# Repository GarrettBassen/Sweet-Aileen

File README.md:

# Sweet-Aileen
Guitar Pedal for Electronics 2 Final Project

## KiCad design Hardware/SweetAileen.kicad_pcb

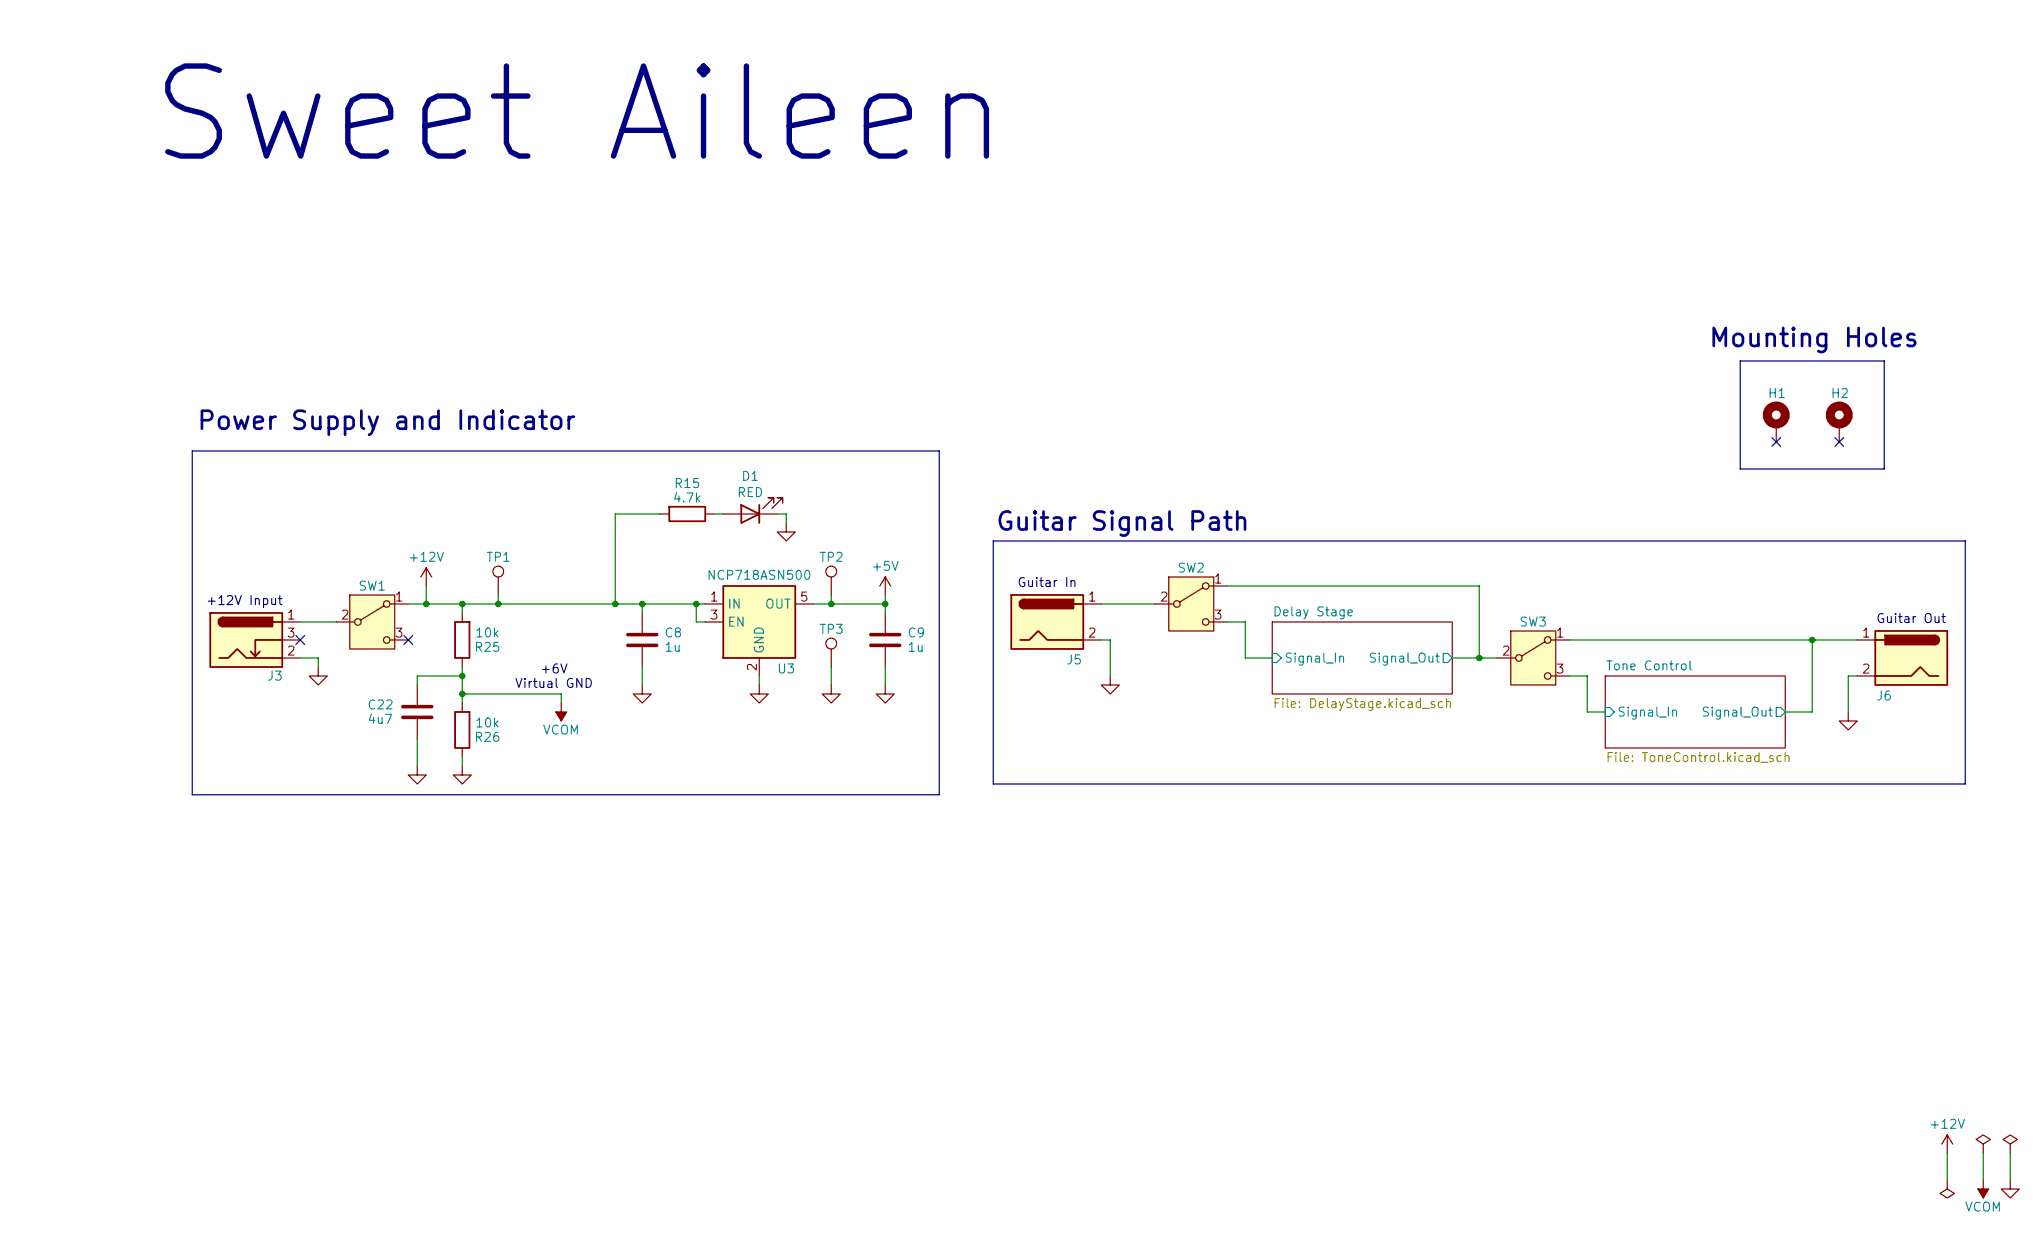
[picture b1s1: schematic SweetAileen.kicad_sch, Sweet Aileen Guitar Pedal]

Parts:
C8, C9: 1u; C_0402_1005Metric
C22: 4u7; C_0805_2012Metric
D1: RED; Connector-Generic-2
H1, H2: MountingHole_Pad; MountingHole_2.5mm_Pad_TopBottom
J3: Barrel_Jack_Switch; 54-00166
J5, J6: Jack-DC; Connector-Generic-2
R15: 4.7k; R_0402_1005Metric
R25, R26: 10k; R_0402_1005Metric
SW1, SW2, SW3: SW_SPDT; Connector-Generic-3
TP1, TP2, TP3: TestPoint; TestPoint_Pad_D1.5mm
U3: NCP718ASN500; SOT-23-5

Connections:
+5V: C9.2, TP2.1 (1_1), U3.5 (OUT); also elsewhere on the board
+12V: C8.2, R15.2, R25.2, SW1.1 (A), TP1.1 (1_1), U3.1 (IN), U3.3 (EN); also elsewhere on the board
/Delay Stage/Signal_In: SW2.3 (C); also elsewhere on the board
/Delay Stage/Signal_Out: SW2.1 (A), SW3.2 (B); also elsewhere on the board
/Tone Control/Signal_In: SW3.3 (C); also elsewhere on the board
/Tone Control/Signal_Out: J6.1, SW3.1 (A); also elsewhere on the board
GND: C8.1, C9.1, C22.1, D1.1 (K), J3.2, J5.2, J6.2, R26.1, TP3.1 (1_1), U3.2 (GND); also elsewhere on the board
unnamed: D1.2 (A), R15.1
unnamed: J3.1, SW1.2 (B)
unnamed: J5.1, SW2.2 (B)
VCOM: C22.2, R25.1, R26.2; also elsewhere on the board

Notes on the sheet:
+6V Virtual GND
Sweet Aileen
Guitar Signal Path
Mounting Holes
Power Supply and Indicator
Guitar In
Guitar Out
+12V Input

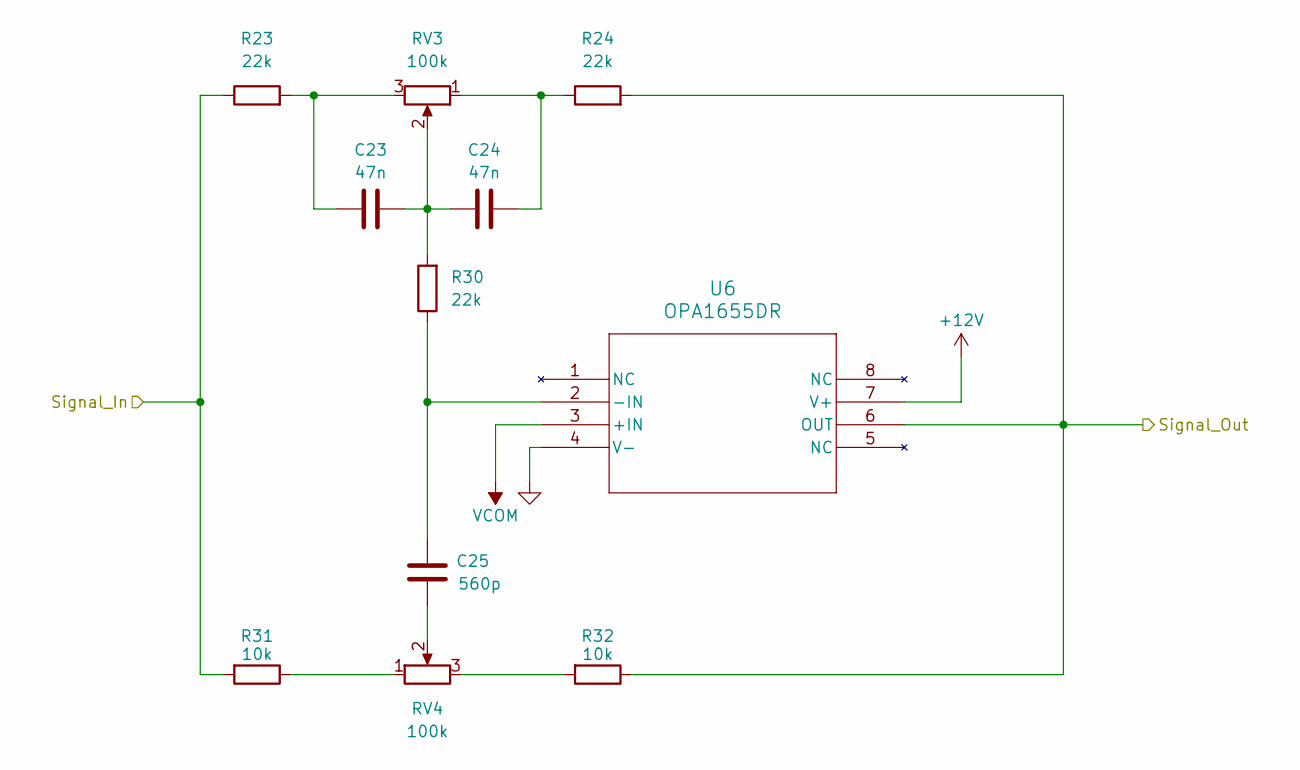
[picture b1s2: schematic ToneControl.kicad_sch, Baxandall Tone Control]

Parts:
C23, C24: 47n; C_0201_0603Metric
C25: 560p; C_0201_0603Metric
R23, R24, R30: 22k; R_0402_1005Metric
R31, R32: 10k; R_0402_1005Metric
RV3, RV4: 100k; Connector-Generic-3
U6: OPA1655DR

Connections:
+12V: U6.7 (V+); also elsewhere on the board
/Tone Control/Signal_In: R23.1, R31.2; also elsewhere on the board
/Tone Control/Signal_Out: R24.2, R32.1, U6.6 (OUT); also elsewhere on the board
GND: U6.4 (V-); also elsewhere on the board
unnamed: C23.1, R23.2, RV3.3
unnamed: C23.2, C24.1, R30.2, RV3.2
unnamed: C24.2, R24.1, RV3.1
unnamed: C25.2, RV4.2
unnamed: R31.1, RV4.1
unnamed: R32.2, RV4.3
unnamed: C25.1, R30.1, U6.2 (-IN)
VCOM: U6.3 (+IN); also elsewhere on the board

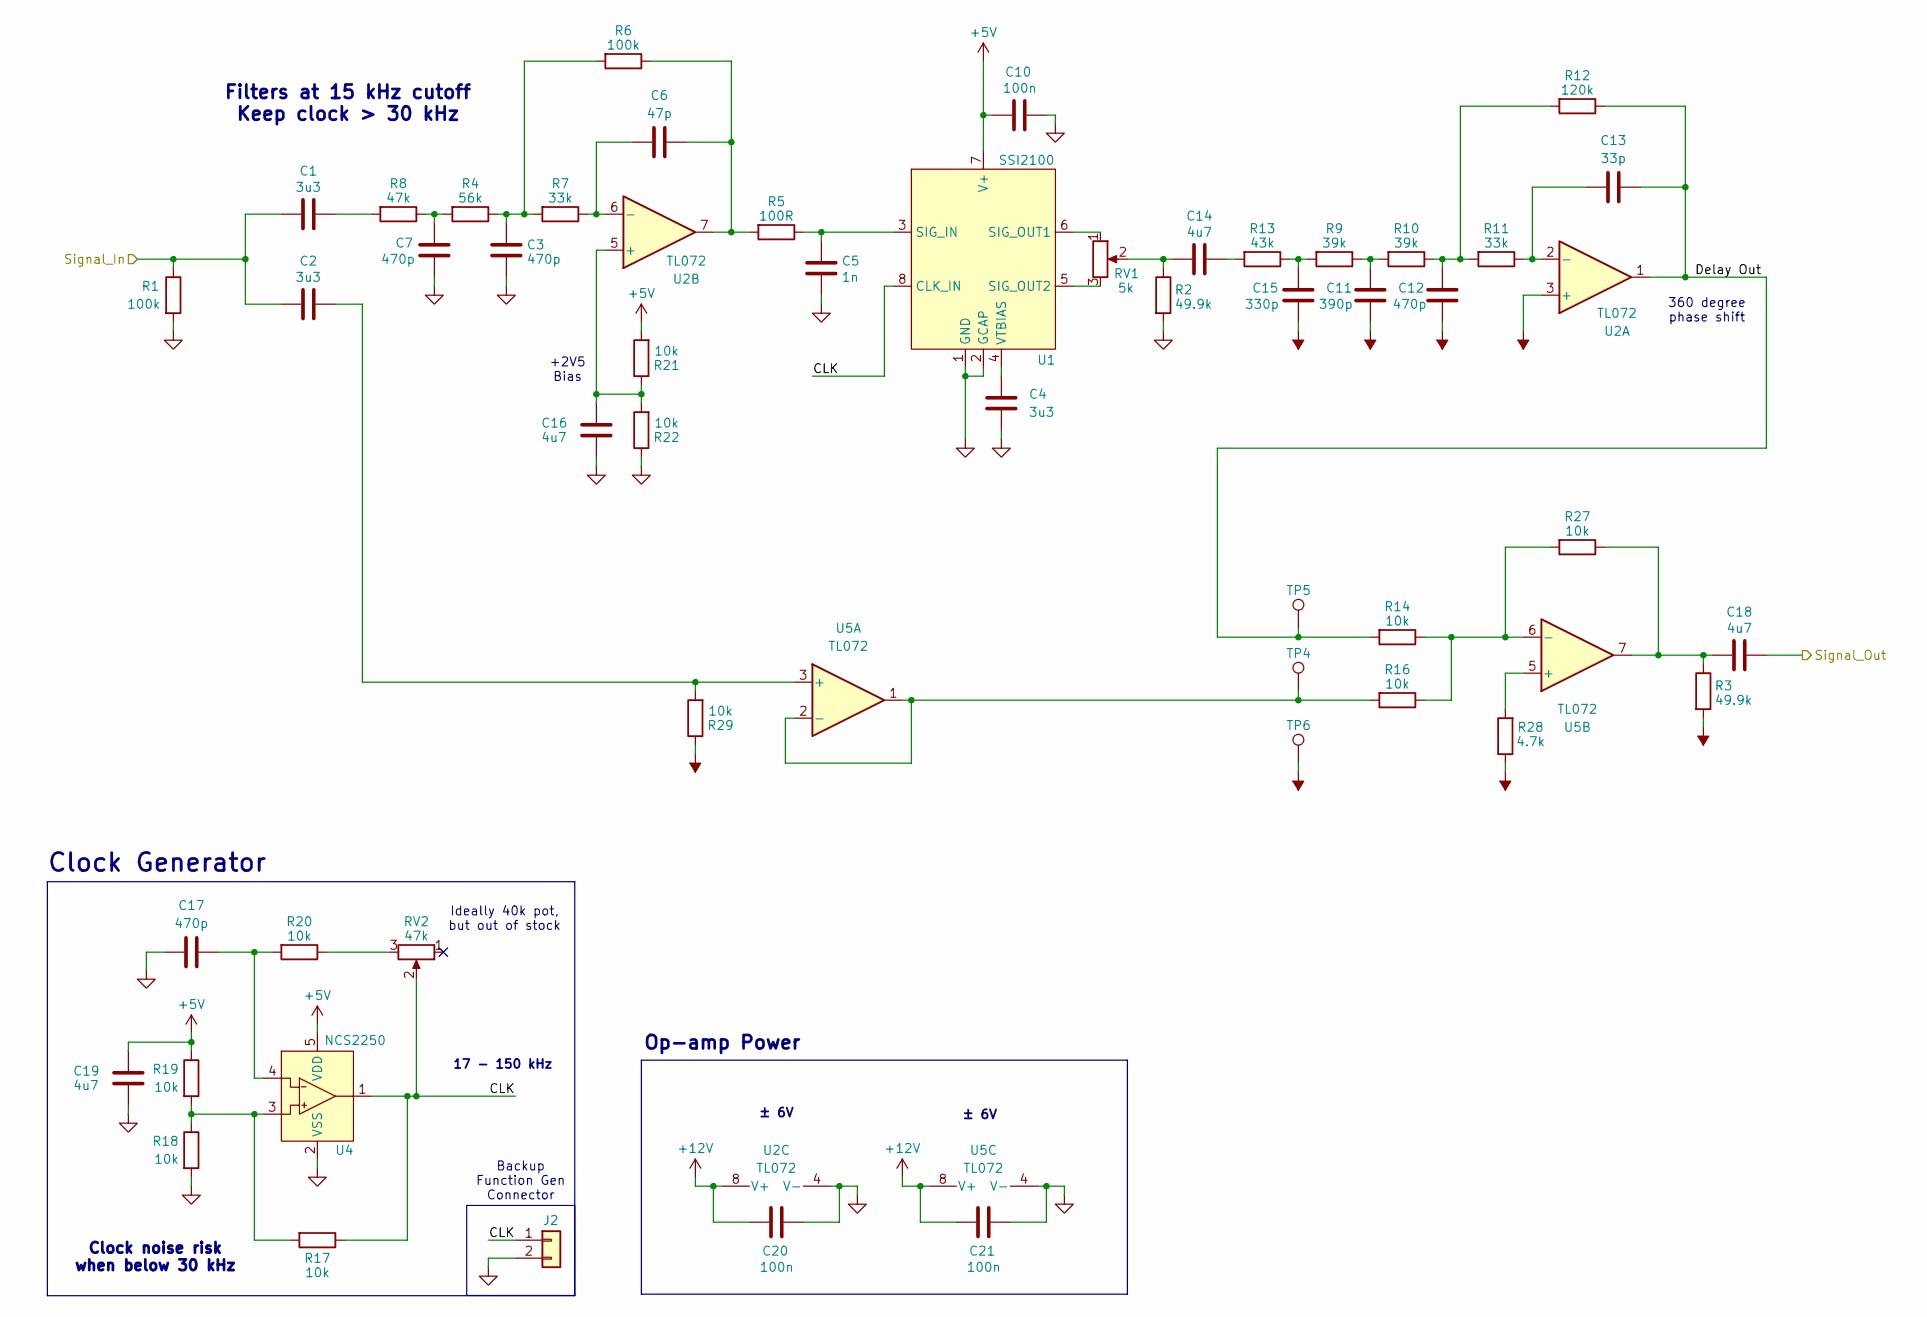
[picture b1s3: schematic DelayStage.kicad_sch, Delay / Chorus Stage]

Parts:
C1, C2, C4: 3u3; C_0805_2012Metric
C3, C7, C12, C17: 470p; C_0201_0603Metric
C5: 1n; C_0201_0603Metric
C6: 47p; C_0201_0603Metric
C10, C20, C21: 100n; C_0402_1005Metric
C11: 390p; C_0201_0603Metric
C13: 33p; C_0201_0603Metric
C14, C16, C18, C19: 4u7; C_0805_2012Metric
C15: 330p; C_0201_0603Metric
J2: Conn_01x02; Connector-Generic-2
R1, R6: 100k; R_0402_1005Metric
R2, R3: 49.9k; R_0402_1005Metric
R4: 56k; R_0402_1005Metric
R5: 100R; R_0402_1005Metric
R7, R11: 33k; R_0402_1005Metric
R8: 47k; R_0402_1005Metric
R9, R10: 39k; R_0402_1005Metric
R12: 120k; R_0402_1005Metric
R13: 43k; R_0402_1005Metric
R14, R16, R17, R18, R19, R20, R21, R22, R27, R29: 10k; R_0402_1005Metric
R28: 4.7k; R_0402_1005Metric
RV1: 5k; 3314G-1_BRN
RV2: 47k; Connector-Generic-3
TP4, TP5, TP6: TestPoint; TestPoint_Pad_D1.5mm
U1: SSI2100
U2, U5: TL072; SOIC-8_3.9x4.9mm_P1.27mm
U4: NCS2250; SOT-353_SC-70-5

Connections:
+5V: C10.2, C19.2, R19.1, R21.2, U1.7 (V+), U4.5 (VDD); also elsewhere on the board
+12V: C20.1, C21.1, U2.8 (V+), U5.8 (V+); also elsewhere on the board
/Delay Stage/CLK: J2.1, R17.1, RV2.2, U1.8 (CLK_IN), U4.1
/Delay Stage/Delay Out: C13.1, R12.1, R14.2, TP5.1 (1_1), U2.1
/Delay Stage/Signal_In: C1.1, C2.1, R1.1; also elsewhere on the board
/Delay Stage/Signal_Out: C18.2; also elsewhere on the board
GND: C3.1, C4.1, C5.1, C7.1, C10.1, C16.1, C17.2, C19.1, C20.2, C21.2, J2.2, R1.2, R2.2, R18.2, R22.1, U1.1 (GND), U1.2 (GCAP), U2.4 (V-), U4.2 (VSS), U5.4 (V-); also elsewhere on the board
unnamed: C1.2, R8.2
unnamed: C3.2, R4.1, R6.2, R7.2
unnamed: C6.1, R5.2, R6.1, U2.7
unnamed: C7.2, R4.2, R8.1
unnamed: C11.2, R9.1, R10.2
unnamed: C12.2, R10.1, R11.2, R12.2
unnamed: C14.1, R2.1, RV1.2
unnamed: C14.2, R13.2
unnamed: C15.2, R9.2, R13.1
unnamed: C17.1, R20.2, U4.4
unnamed: C18.1, R3.1, R27.1, U5.7
unnamed: R17.2, R18.1, R19.2, U4.3
unnamed: R20.1, RV2.3
unnamed: C5.2, R5.1, U1.3 (SIG_IN)
unnamed: RV1.1, U1.6 (SIG_OUT1)
unnamed: RV1.3, U1.5 (SIG_OUT2)
unnamed: C4.2, U1.4 (VTBIAS)
unnamed: C13.2, R11.1, U2.2 (-)
unnamed: C16.2, R21.1, R22.2, U2.5 (+)
unnamed: C6.2, R7.1, U2.6 (-)
unnamed: C2.2, R29.2, U5.3 (+)
unnamed: R16.2, TP4.1 (1_1), U5.1, U5.2 (-)
unnamed: R28.2, U5.5 (+)
unnamed: R14.1, R16.1, R27.2, U5.6 (-)
VCOM: C11.1, C12.1, C15.1, R3.2, R28.1, R29.1, TP6.1 (1_1), U2.3 (+); also elsewhere on the board

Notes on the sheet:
Ideally 40k pot, but out of stock
17 - 150 kHz
Clock Generator
± 6V
Backup Function Gen Connector
Op-amp Power
Filters at 15 kHz cutoff Keep clock > 30 kHz
+2V5 Bias
360 degree phase shift
Clock noise risk when below 30 kHz

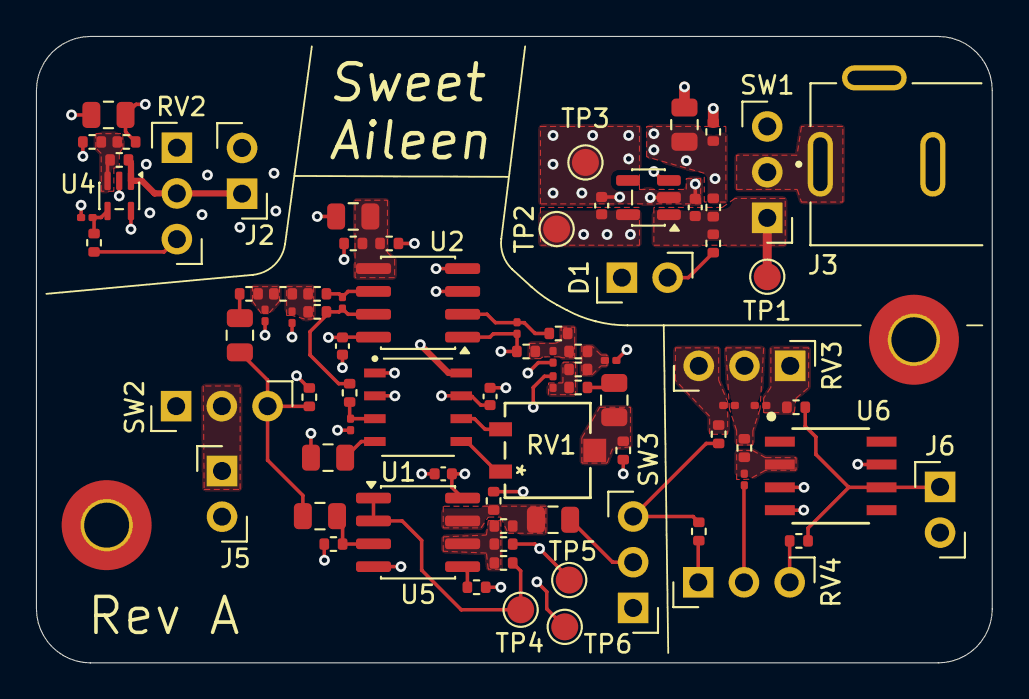
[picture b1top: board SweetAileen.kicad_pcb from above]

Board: 4 copper layers, 53.1 x 34.8 mm, 83 parts (0 on the bottom side), 44 nets.
